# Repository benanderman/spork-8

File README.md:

# Spork-8

This is an 8-bit computer project, inspired by [Ben Eater's 8-bit breadboard computer](https://eater.net/8bit). It's made out of modular PCBs that plug into each other, and contain mostly 74HC-series chips (original 74LS). It runs code from an EEPROM (so it's only programmable from a computer), and has separate memory. It's meant to display what's happening, when running on a 555-timer or manually stepping, but also be capable enough to implement some sort of game, when using an oscillator as a clock.

For details about programming the Spork-8, see [Programming.md](Programming.md).

## Status of project

The project was originally completed in 2021 and mostly worked with 74LS-series chips, but it had some issues (see [RevisionLog](RevisionLog.md)), and used way too much power.

In 2025, it was rebuilt with 74HC-series chips, and several improvements, an emulator, and peripheral boards. It had some issues, but mostly worked well.

In 2026, reliability was improved by adding ground planes to the bus boards and control board, the instruction set was improved, and much more complex programs were made.

## Modules
 * **Control module**: Coordinates everything else. Contains the micro-code EEPROMs, instruction register, micro-instruction counter, power input, reset button, and logic to interface with modules through bus boards.
 * **Bus**: Four of these interface between the control module and up to 16 other modules. These demux three signal lines each for in/out enable signals to the four modules connected to each bus board. One bus board plugs into the top of the control module, and one into the bottom. Two more bus boards plug into the first two. The first in/out signal line selects between the two boards on top / bottom, and the one connected to the control module inverts the signal before passing it onto the other bus board.
 * **Register**: Stores 8 bits, and can connect directly to an adjacent board above or below to expose its value (for use by the ALU and shift / rotate module). Has output headers, to interface with peripherals.
 * **ALU**: Performes calculations on values from register modules above and below it. Can output: add, subtract, bit-wise AND, or the carry-bit and zero-flag for any of those operations. Must be placed in the 1111 position (bottom right of top-most bus board), because the control module is hard-wired to input to the flags register when the read signal to that module position is enabled, which also enables flag output on the ALU.
 * **Clock**: Provides the clock pulse for the computer. Has three modes: manual with button to pulse, 555-timer with potentiometer to adjust timing, or crystal oscillator (2MHz seems to work).
 * **Counter**: Stores and counts 16-bit values. Uses two global signal lines to select which byte to read / write, and whether to enable counting. Used for both the RAM address register and program counter / program memory address register.
 * **RAM**: RAM or EEPROM (they have the same pinout). Used for the program memory EEPROM (not intended to be written to), and the static memory used for storing data. Up to 15-bits of address are taken from an adjacent counter module. Also has a cartridge slot, and switches between it and the EEPROM on the board using the 16th address bit. This allows swapping out programs much easier
 * **Input / Output**: Like a register module, except when outputting to the bus, outputs the value from input headers instead of the registers. The 8-bit value stored in the registers is accessible on output headers as well. The two headers are in parallel, making it sturdy to plug in a peripheral that uses both.
 * **Battery**: Has a battery, charging capability with USB-C, and a switch to output power to the CPU.

## Layout

In general, any of the 16 module slots can input from or output to the bus, so most modules could go in any position. However, some of them have to go in specific slots, because:

1. The 0th slot on the top and bottom aren't usable for in/out selection, because it's ambiguous whether that slot is selected or if no module on that side is selected. The battery and clock go in those slots, since they only output power and a clock signal, and don't use the bus.
1. The 8 "custom" signals (that mean something different for different modules) are split up into 4 for top, 4 for bottom. Those 4 are split into pairs; the top 2 modules on each bus board get one pair, and the bottom two get the second pair. The second pair of signals on the bottom is actually used by the control board.
1. Some modules (RAM / ROM, ALU, and Shift) get inputs from other modules, so their inputs have to be next to them.

**Top left**: The program counter goes in the top to use the first pair of custom signals (for count and byte select), plugging into the program memory below it. Below that is the clock (in the 0th position), and Register C.

**Top right**: The ALU goes one slot down from the top, to use the second pair of custom signals (for add/subtract and bit-wise AND), with register A and B as its operands above and below. Then the shift / rotate module goes at the bottom plugging into register B. These need to be on the right side to avoid the 0th position. The shift module shares custom signals with the ALU, which is okay because only one is used at a time, and the signals don't have an effect if that module isn't outputting.

**Bottom left**: The battery takes the top 0th slot, and then the stack and swap registers, and input / output A module after that. Other than the battery, the positions are arbitrary.

**Bottom right**: The output A register goes at the top and the RAM goes below it. The memory address register goes in the next position to get the first pair of custom signals (for count and byte select), and plugs into the RAM above it. The input / output B module goes at the bottom. The memory address could instead go where output A is, and RAM just needs to be next to it. The other two could go anywhere.

## Peripherals
* **Controller Connector**: Plugs into IO module, and has two RJ12 plugs on it, to connect to parallel-to-serial shift register-based controllers.
* **Screen**: An 10x20 595-shift register-based monochrome display. Plugs into output module (vertically), or IO module (horizontally).
* **Cartridge**: A small board with a surface-mount version of the same 28C256 EEPROM used as in the program memory module. Plugs into the program memory module with the smallest PCIe board edge connector.
* **Programmer**: Arduino-based board used to program and test the CPU in 3 ways:
    1. Separate from the CPU, read / write to EEPROMs (big ones, or cartridges).
    2. Plug into bus boards, to test all the modules plugged in (doesn't work, because the bus is needed to set the signals, but that could cause bus contention).
    3. Replace the program memory and clock, to have a very fast development cycle to write program code (not necessary now that there's an emulator), or to test the CPU.
 
## Layout, signals, and parts list
These images show the layout of the modules in the 16 slots, the functions of each of the signals, and a parts list.

## Design images
### Overall layout

### Mounting board (laser cut acrylic)

### Schematics

### PCB Layouts

### 3D Renderings

## Contributing

### Compiling Assembly Files

Dependency: [customasm](https://hlorenzi.github.io/customasm/)

```
cd Code/emulator
customasm ../programs/snake2p.asm -o ../programs/snake2p.bin -f binary
```

Then pass the .bin files to the emulator.

### Compiling and Running the Emulator

```
cd Code/emulator
zig build
./zig-out/bin/emulator ../programs/snake2p.bin
```

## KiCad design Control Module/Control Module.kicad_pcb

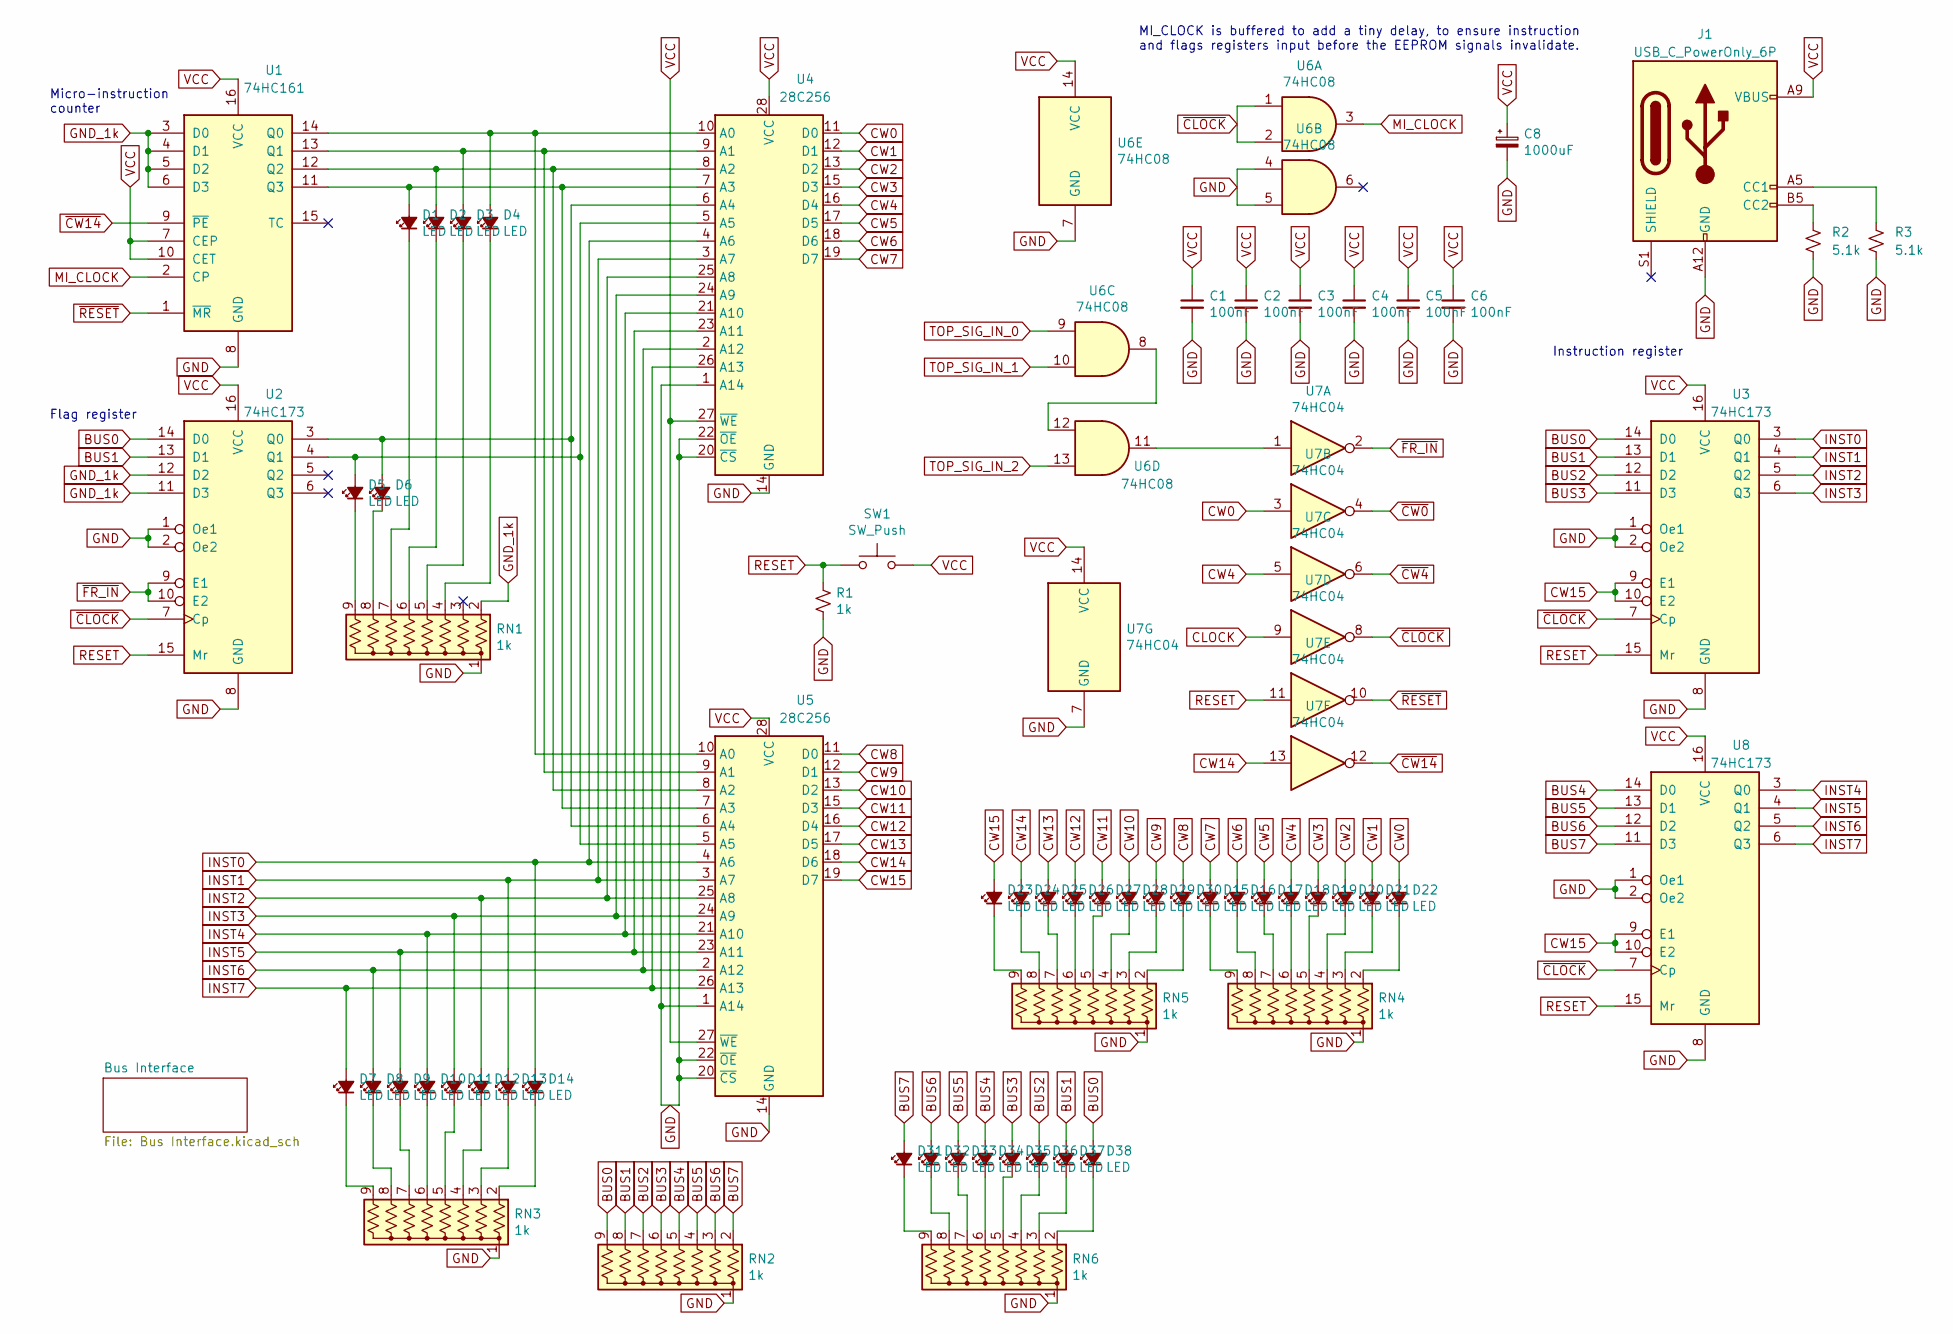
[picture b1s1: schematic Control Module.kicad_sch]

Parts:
C1, C2, C3, C4, C5, C6: 100nF; C_Disc_D4.3mm_W1.9mm_P5.00mm
C8: 1000uF; CP_Radial_D8.0mm_P3.50mm
D1, D2, D3, D4, D5, D6, D7, D8, D9, D10, D11, D12, D13, D14, D15, D16, D17, D18, D19, D20, D21, D22, D23, D24, D25, D26, D27, D28, D29, D30, D31, D32, D33, D34, D35, D36, D37, D38: LED; LED_D3.0mm
J1: USB_C_PowerOnly_6P; USB_C_Receptacle_G-Switch_GT-USB-7010ASV; LCSC C2988369
R1: 1k; R_Axial_DIN0207_L6.3mm_D2.5mm_P7.62mm_Horizontal
R2, R3: 5.1k; R_0603_1608Metric
RN1, RN2, RN3, RN4, RN5, RN6: 1k; R_Array_SIP9
SW1: SW_Push; SW_PUSH_6mm
U1: 74HC161; DIP-16_W7.62mm
U2, U3, U8: 74HC173; DIP-16_W7.62mm
U4, U5: 28C256; DIP-28_W15.24mm_Socket
U6: 74HC08; DIP-14_W7.62mm
U7: 74HC04; DIP-14_W7.62mm

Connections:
BUS0: D38.2 (A), RN2.9 (R8), U2.14 (D0), U3.14 (D0); also elsewhere on the board
BUS1: D37.2 (A), RN2.8 (R7), U2.13 (D1), U3.13 (D1); also elsewhere on the board
BUS2: D36.2 (A), RN2.7 (R6), U3.12 (D2); also elsewhere on the board
BUS3: D35.2 (A), RN2.6 (R5), U3.11 (D3); also elsewhere on the board
BUS4: D34.2 (A), RN2.5 (R4), U8.14 (D0); also elsewhere on the board
BUS5: D33.2 (A), RN2.4 (R3), U8.13 (D1); also elsewhere on the board
BUS6: D32.2 (A), RN2.3 (R2), U8.12 (D2); also elsewhere on the board
BUS7: D31.2 (A), RN2.2 (R1), U8.11 (D3); also elsewhere on the board
CLOCK: U7.9; also elsewhere on the board
CW0: D22.2 (A), U4.11 (D0), U7.3; also elsewhere on the board
CW1: D21.2 (A), U4.12 (D1); also elsewhere on the board
CW2: D20.2 (A), U4.13 (D2); also elsewhere on the board
CW3: D19.2 (A), U4.15 (D3); also elsewhere on the board
CW4: D18.2 (A), U4.16 (D4), U7.5; also elsewhere on the board
CW5: D17.2 (A), U4.17 (D5); also elsewhere on the board
CW6: D16.2 (A), U4.18 (D6); also elsewhere on the board
CW7: D15.2 (A), U4.19 (D7); also elsewhere on the board
CW8: D30.2 (A), U5.11 (D0); also elsewhere on the board
CW9: D29.2 (A), U5.12 (D1); also elsewhere on the board
CW10: D28.2 (A), U5.13 (D2); also elsewhere on the board
CW11: D27.2 (A), U5.15 (D3); also elsewhere on the board
CW12: D26.2 (A), U5.16 (D4); also elsewhere on the board
CW13: D25.2 (A), U5.17 (D5); also elsewhere on the board
CW14: D24.2 (A), U5.18 (D6), U7.13; also elsewhere on the board
CW15: D23.2 (A), U3.9 (E1), U3.10 (E2), U5.19 (D7), U8.9 (E1), U8.10 (E2); also elsewhere on the board
GND: C1.2, C2.2, C3.2, C4.2, C5.2, C6.2, C8.2, J1.A12 (GND), J1.B12 (GND), R1.2, R2.2, R3.2, RN1.1 (common), RN2.1 (common), RN3.1 (common), RN4.1 (common), RN5.1 (common), RN6.1 (common), U1.8 (GND), U2.1 (Oe1), U2.2 (Oe2), U2.8 (GND), U3.1 (Oe1), U3.2 (Oe2), U3.8 (GND), U4.1 (A14), U4.14 (GND), U4.20 (~CS), U4.22 (~OE), U5.1 (A14), U5.14 (GND), U5.20 (~CS), U5.22 (~OE), U6.4, U6.5, U6.7 (GND), U7.7 (GND), U8.1 (Oe1), U8.2 (Oe2), U8.8 (GND); also elsewhere on the board
GND_1k: RN1.2 (R1), U1.3 (D0), U1.4 (D1), U1.5 (D2), U1.6 (D3), U2.11 (D3), U2.12 (D2)
INST0: D14.2 (A), U3.3 (Q0), U4.4 (A6), U5.4 (A6)
INST1: D13.2 (A), U3.4 (Q1), U4.3 (A7), U5.3 (A7)
INST2: D12.2 (A), U3.5 (Q2), U4.25 (A8), U5.25 (A8)
INST3: D11.2 (A), U3.6 (Q3), U4.24 (A9), U5.24 (A9)
INST4: D10.2 (A), U4.21 (A10), U5.21 (A10), U8.3 (Q0)
INST5: D9.2 (A), U4.23 (A11), U5.23 (A11), U8.4 (Q1)
INST6: D8.2 (A), U4.2 (A12), U5.2 (A12), U8.5 (Q2)
INST7: D7.2 (A), U4.26 (A13), U5.26 (A13), U8.6 (Q3)
MI_CLOCK: U1.2 (CP), U6.3
unnamed: D1.2 (A), U1.11 (Q3), U4.7 (A3), U5.7 (A3)
unnamed: D1.1 (K), RN1.7 (R6)
unnamed: D2.2 (A), U1.12 (Q2), U4.8 (A2), U5.8 (A2)
unnamed: D2.1 (K), RN1.6 (R5)
unnamed: D3.2 (A), U1.13 (Q1), U4.9 (A1), U5.9 (A1)
unnamed: D3.1 (K), RN1.5 (R4)
unnamed: D4.2 (A), U1.14 (Q0), U4.10 (A0), U5.10 (A0)
unnamed: D4.1 (K), RN1.4 (R3)
unnamed: D5.2 (A), U2.4 (Q1), U4.5 (A5), U5.5 (A5)
unnamed: D5.1 (K), RN1.9 (R8)
unnamed: D6.2 (A), U2.3 (Q0), U4.6 (A4), U5.6 (A4)
unnamed: D6.1 (K), RN1.8 (R7)
unnamed: D7.1 (K), RN3.9 (R8)
unnamed: D8.1 (K), RN3.8 (R7)
unnamed: D9.1 (K), RN3.7 (R6)
unnamed: D10.1 (K), RN3.6 (R5)
unnamed: D11.1 (K), RN3.5 (R4)
unnamed: D12.1 (K), RN3.4 (R3)
unnamed: D13.1 (K), RN3.3 (R2)
unnamed: D14.1 (K), RN3.2 (R1)
unnamed: D15.1 (K), RN4.9 (R8)
unnamed: D16.1 (K), RN4.8 (R7)
unnamed: D17.1 (K), RN4.7 (R6)
unnamed: D18.1 (K), RN4.6 (R5)
unnamed: D19.1 (K), RN4.5 (R4)
unnamed: D20.1 (K), RN4.4 (R3)
unnamed: D21.1 (K), RN4.3 (R2)
unnamed: D22.1 (K), RN4.2 (R1)
unnamed: D23.1 (K), RN5.9 (R8)
unnamed: D24.1 (K), RN5.8 (R7)
unnamed: D25.1 (K), RN5.7 (R6)
unnamed: D26.1 (K), RN5.6 (R5)
unnamed: D27.1 (K), RN5.5 (R4)
unnamed: D28.1 (K), RN5.4 (R3)
unnamed: D29.1 (K), RN5.3 (R2)
unnamed: D30.1 (K), RN5.2 (R1)
unnamed: D31.1 (K), RN6.9 (R8)
unnamed: D32.1 (K), RN6.8 (R7)
unnamed: D33.1 (K), RN6.7 (R6)
unnamed: D34.1 (K), RN6.6 (R5)
unnamed: D35.1 (K), RN6.5 (R4)
unnamed: D36.1 (K), RN6.4 (R3)
unnamed: D37.1 (K), RN6.3 (R2)
unnamed: D38.1 (K), RN6.2 (R1)
unnamed: J1.A5 (CC1), R3.1
unnamed: J1.B5 (CC2), R2.1
unnamed: U6.11, U7.1
unnamed: U6.8, U6.12
RESET: R1.1, SW1.1, U2.15 (Mr), U3.15 (Mr), U7.11, U8.15 (Mr); also elsewhere on the board
TOP_SIG_IN_0: U6.9; also elsewhere on the board
TOP_SIG_IN_1: U6.10; also elsewhere on the board
TOP_SIG_IN_2: U6.13; also elsewhere on the board
VCC: C1.1, C2.1, C3.1, C4.1, C5.1, C6.1, C8.1, J1.A9 (VBUS), J1.B9 (VBUS), SW1.2, U1.7 (CEP), U1.10 (CET), U1.16 (VCC), U2.16 (VCC), U3.16 (VCC), U4.27 (~WE), U4.28 (VCC), U5.27 (~WE), U5.28 (VCC), U6.14 (VCC), U7.14 (VCC), U8.16 (VCC); also elsewhere on the board
~CLOCK: U2.7 (Cp), U3.7 (Cp), U6.1, U6.2, U7.8, U8.7 (Cp)
~CW0: U7.4; also elsewhere on the board
~CW4: U7.6; also elsewhere on the board
~CW14: U1.9 (~PE), U7.12
~FR_IN: U2.9 (E1), U2.10 (E2), U7.2
~RESET: U1.1 (~MR), U7.10

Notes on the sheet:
Micro-instruction counter
MI_CLOCK is buffered to add a tiny delay, to ensure instruction and flags registers input before the EEPROM signals invalidate.
Flag register
Instruction register

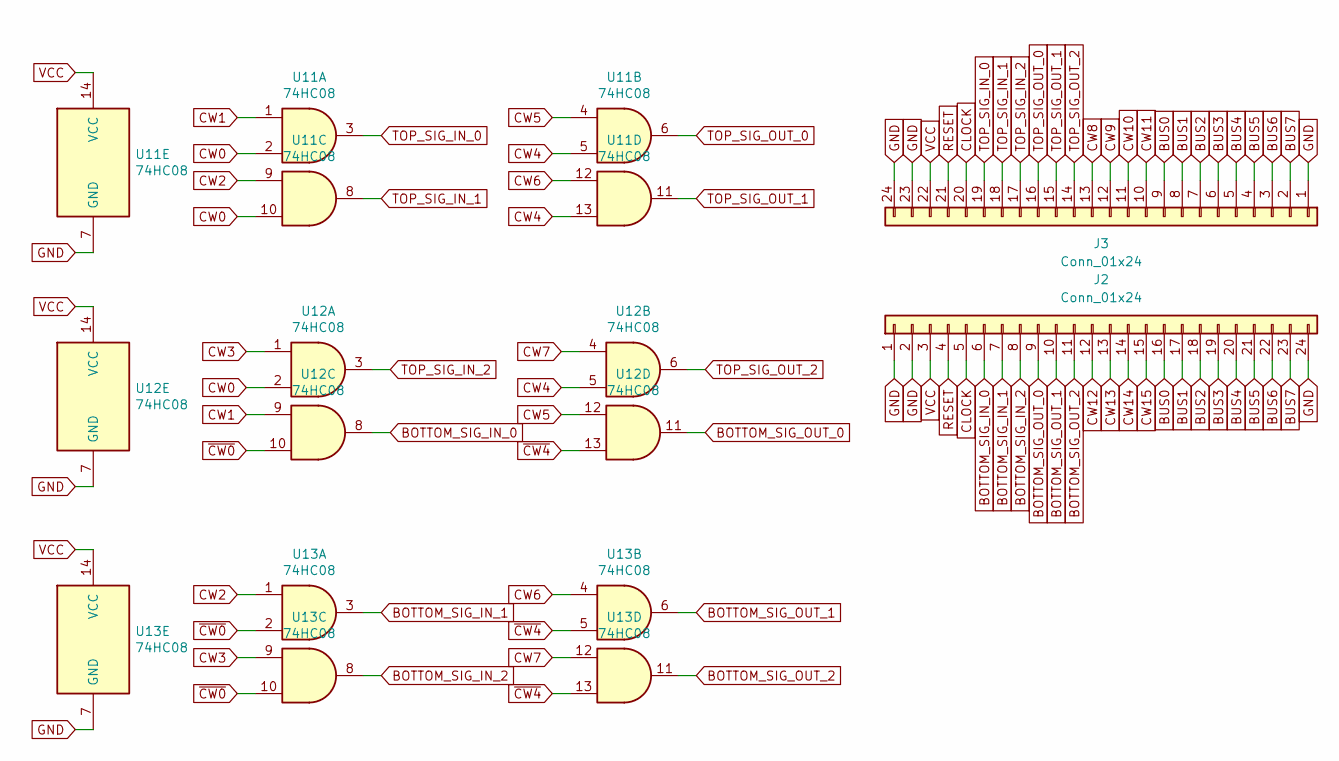
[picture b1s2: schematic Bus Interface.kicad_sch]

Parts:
J2, J3: Conn_01x24; PinSocket_1x24_P2.54mm_Horizontal
U11, U12, U13: 74HC08; DIP-14_W7.62mm

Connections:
BOTTOM_SIG_IN_0: J2.6, U12.8
BOTTOM_SIG_IN_1: J2.7, U13.3
BOTTOM_SIG_IN_2: J2.8, U13.8
BOTTOM_SIG_OUT_0: J2.9, U12.11
BOTTOM_SIG_OUT_1: J2.10, U13.6
BOTTOM_SIG_OUT_2: J2.11, U13.11
BUS0: J2.16, J3.9; also elsewhere on the board
BUS1: J2.17, J3.8; also elsewhere on the board
BUS2: J2.18, J3.7; also elsewhere on the board
BUS3: J2.19, J3.6; also elsewhere on the board
BUS4: J2.20, J3.5; also elsewhere on the board
BUS5: J2.21, J3.4; also elsewhere on the board
BUS6: J2.22, J3.3; also elsewhere on the board
BUS7: J2.23, J3.2; also elsewhere on the board
CLOCK: J2.5, J3.20; also elsewhere on the board
CW0: U11.2, U11.10, U12.2; also elsewhere on the board
CW1: U11.1, U12.9; also elsewhere on the board
CW2: U11.9, U13.1; also elsewhere on the board
CW3: U12.1, U13.9; also elsewhere on the board
CW4: U11.5, U11.13, U12.5; also elsewhere on the board
CW5: U11.4, U12.12; also elsewhere on the board
CW6: U11.12, U13.4; also elsewhere on the board
CW7: U12.4, U13.12; also elsewhere on the board
CW8: J3.13; also elsewhere on the board
CW9: J3.12; also elsewhere on the board
CW10: J3.11; also elsewhere on the board
CW11: J3.10; also elsewhere on the board
CW12: J2.12; also elsewhere on the board
CW13: J2.13; also elsewhere on the board
CW14: J2.14; also elsewhere on the board
CW15: J2.15; also elsewhere on the board
GND: J2.1, J2.2, J2.24, J3.1, J3.23, J3.24, U11.7 (GND), U12.7 (GND), U13.7 (GND); also elsewhere on the board
RESET: J2.4, J3.21; also elsewhere on the board
TOP_SIG_IN_0: J3.19, U11.3; also elsewhere on the board
TOP_SIG_IN_1: J3.18, U11.8; also elsewhere on the board
TOP_SIG_IN_2: J3.17, U12.3; also elsewhere on the board
TOP_SIG_OUT_0: J3.16, U11.6
TOP_SIG_OUT_1: J3.15, U11.11
TOP_SIG_OUT_2: J3.14, U12.6
VCC: J2.3, J3.22, U11.14 (VCC), U12.14 (VCC), U13.14 (VCC); also elsewhere on the board
~CW0: U12.10, U13.2, U13.10; also elsewhere on the board
~CW4: U12.13, U13.5, U13.13; also elsewhere on the board

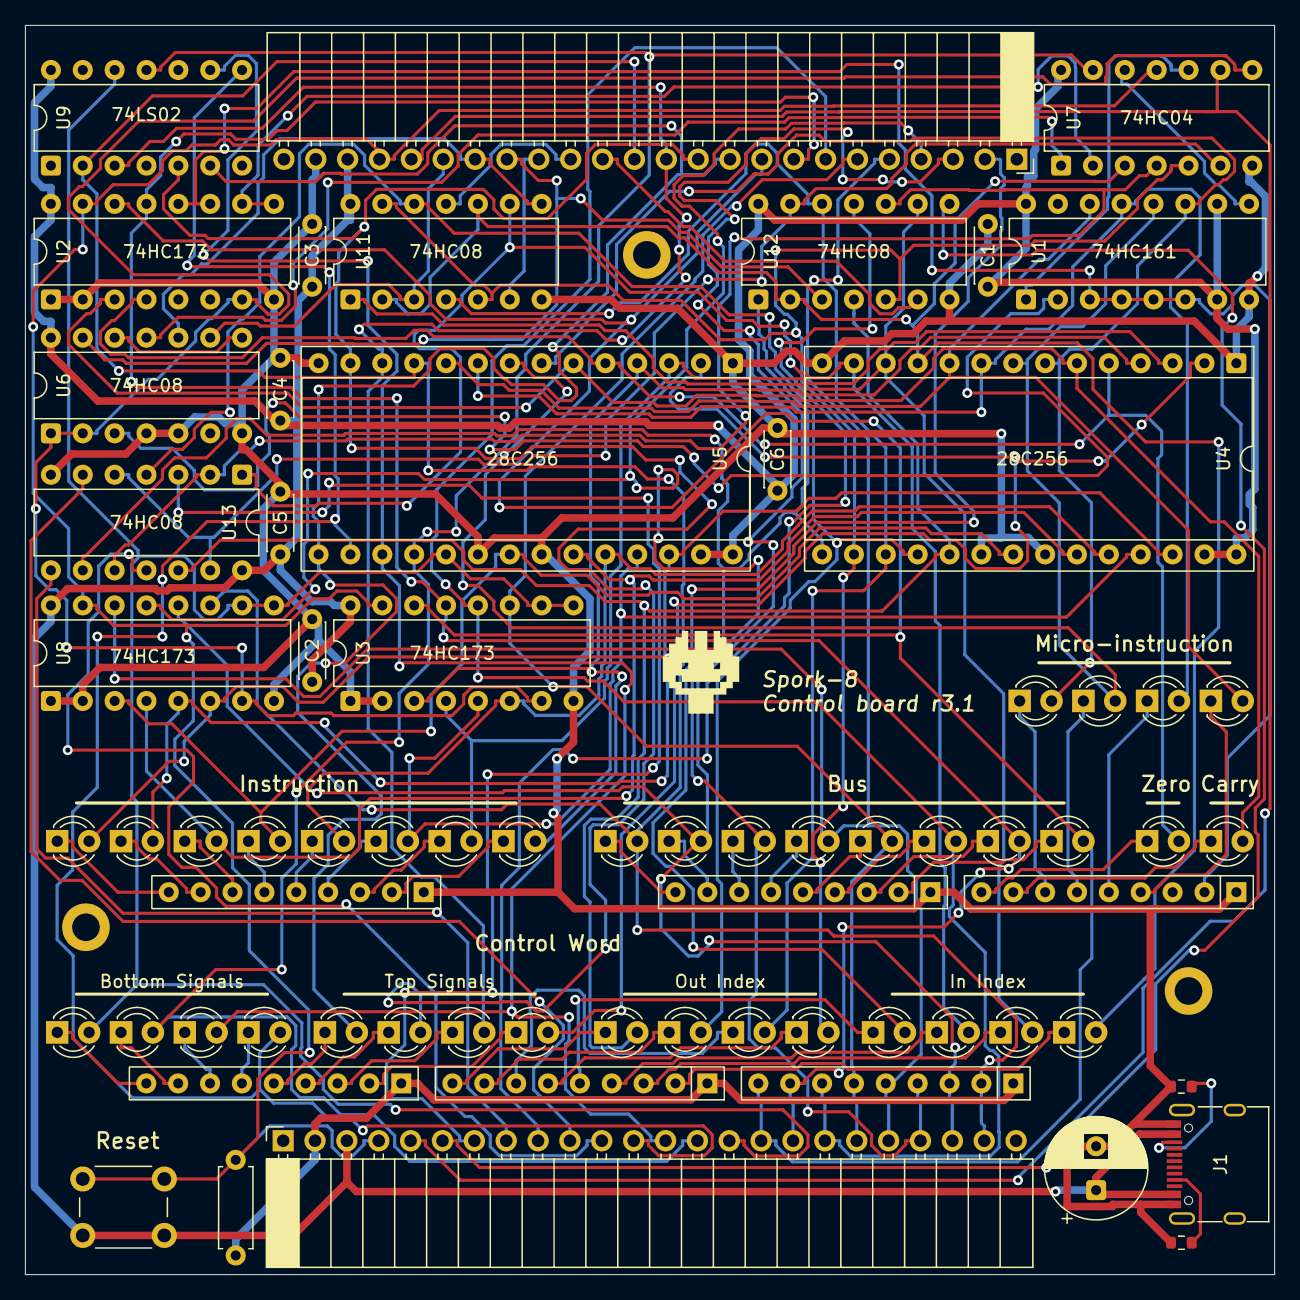
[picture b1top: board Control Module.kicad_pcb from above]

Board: 4 copper layers, 99.6 x 99.6 mm, 73 parts (0 on the bottom side), 104 nets.

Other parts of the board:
HOLE1, HOLE2, HOLE3: MountingHole_2.2mm_M2_DIN965_Pad
U9: 74LS02; DIP-14_W7.62mm

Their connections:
CW8: U9.2; also elsewhere on the board
CW9: U9.3; also elsewhere on the board
CW10: U9.5; also elsewhere on the board
CW11: U9.6; also elsewhere on the board
CW12: U9.8; also elsewhere on the board
CW13: U9.9; also elsewhere on the board
CW14: U9.11; also elsewhere on the board
CW15: U9.12; also elsewhere on the board
GND: U9.7; also elsewhere on the board
VCC: U9.14; also elsewhere on the board

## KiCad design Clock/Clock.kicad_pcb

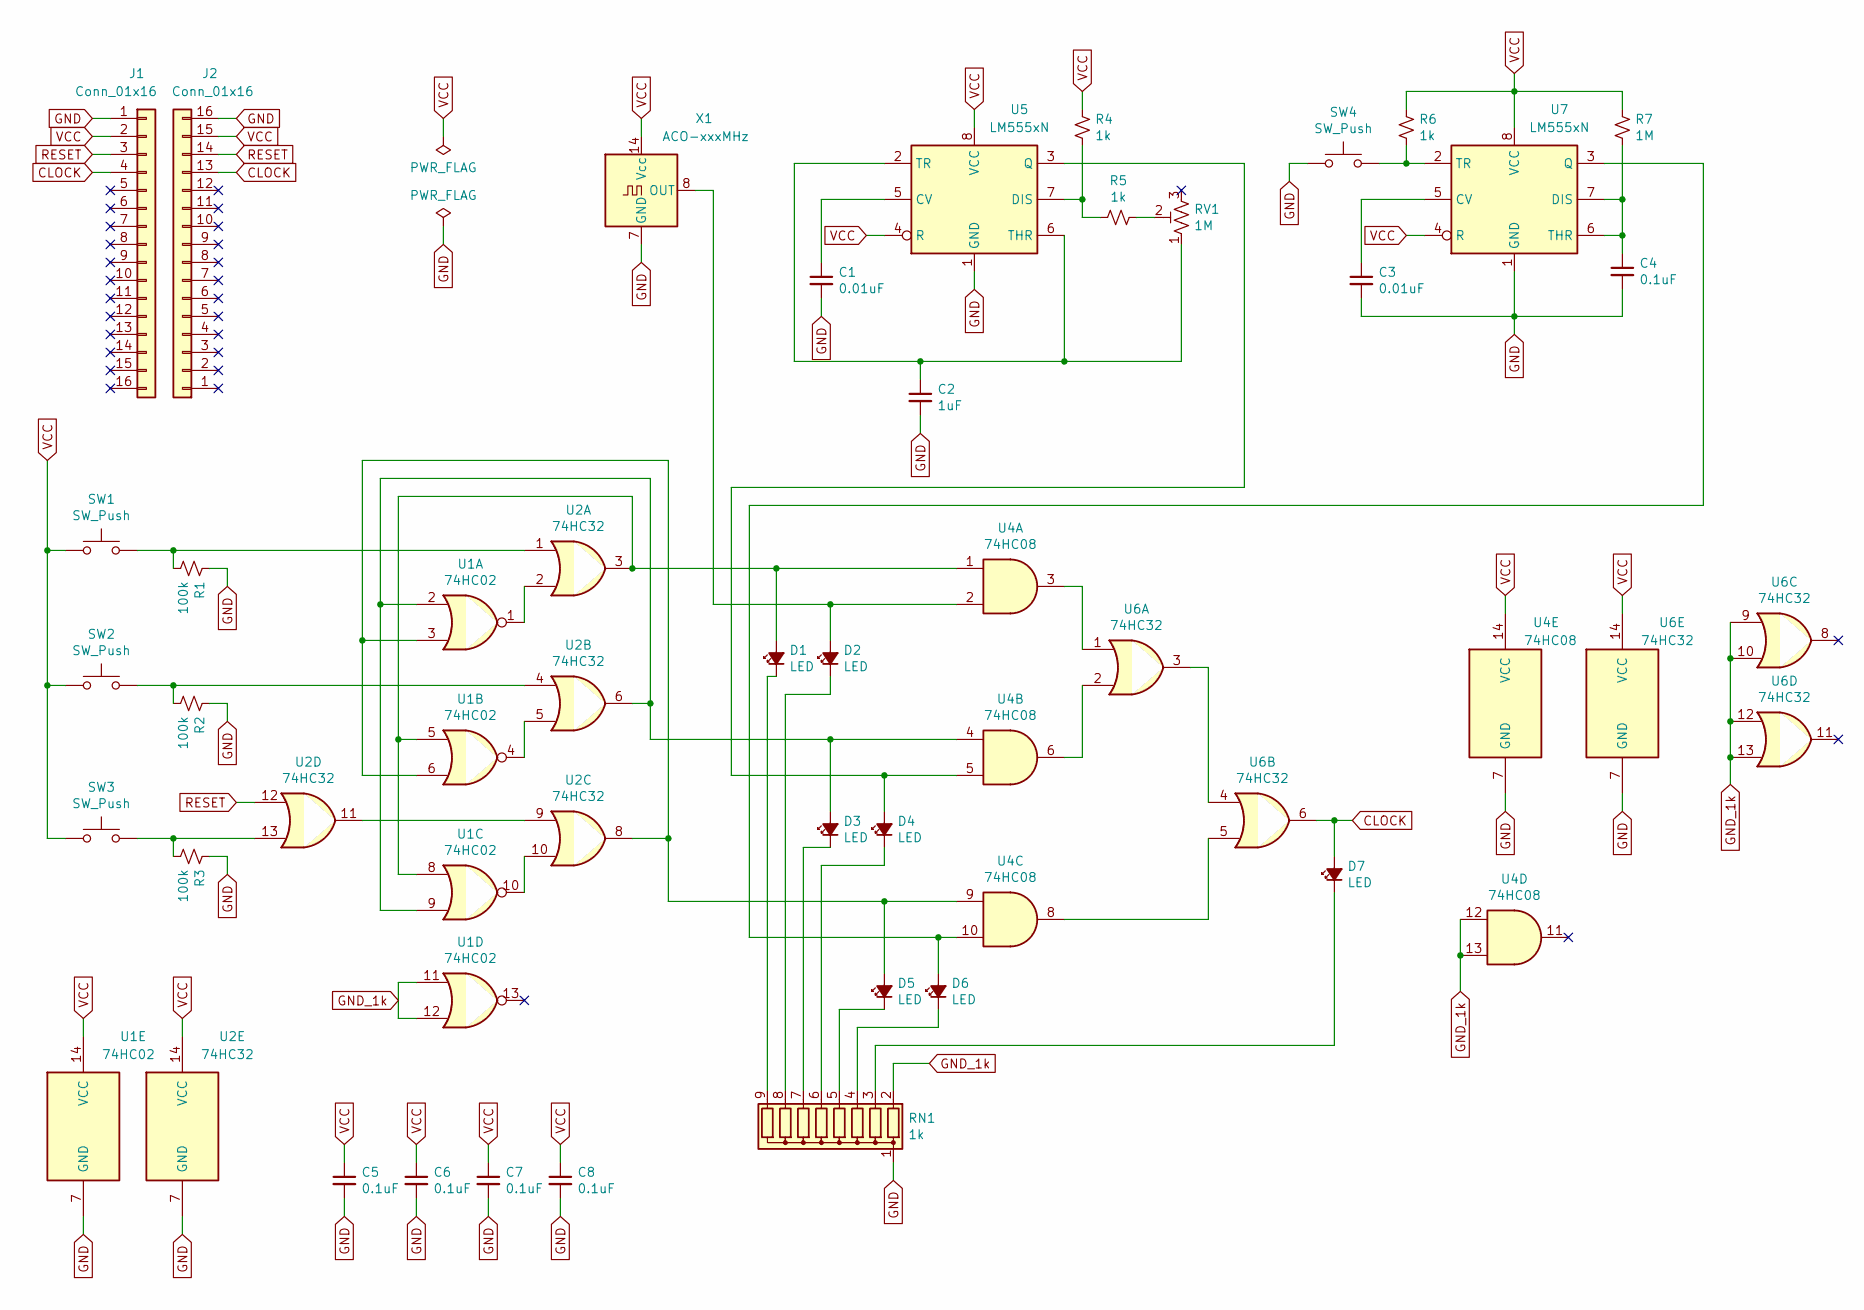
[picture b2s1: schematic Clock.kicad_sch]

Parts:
C1, C3: 0.01uF; C_Disc_D4.3mm_W1.9mm_P5.00mm
C2: 1uF; C_Disc_D4.3mm_W1.9mm_P5.00mm
C4, C5, C6, C7, C8: 0.1uF; C_Disc_D4.3mm_W1.9mm_P5.00mm
D1, D2, D3, D4, D5, D6, D7: LED; LED_D3.0mm_Clear
J1, J2: Conn_01x16; PinHeader_1x16_P2.54mm_Horizontal
R1, R2, R3: 100k; R_Axial_DIN0207_L6.3mm_D2.5mm_P7.62mm_Horizontal
R4, R5, R6: 1k; R_Axial_DIN0207_L6.3mm_D2.5mm_P7.62mm_Horizontal
R7: 1M; R_Axial_DIN0207_L6.3mm_D2.5mm_P7.62mm_Horizontal
RN1: 1k; R_Array_SIP9
RV1: 1M; Potentiometer_Bourns_PTV09A-1_Single_Vertical
SW1, SW2, SW3, SW4: SW_Push; SW_PUSH_6mm
U1: 74HC02; DIP-14_W7.62mm
U2, U6: 74HC32; DIP-14_W7.62mm
U4: 74HC08; DIP-14_W7.62mm
U5, U7: LM555xN; DIP-8_W7.62mm
X1: ACO-xxxMHz; Oscillator_DIP-14

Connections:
CLOCK: D7.2 (A), J1.4, J2.13, U6.6
GND: C1.2, C2.2, C3.2, C4.2, C5.2, C6.2, C7.2, C8.2, J1.1, J2.16, R1.1, R2.1, R3.1, RN1.1 (common), SW4.1, U1.7 (GND), U2.7 (GND), U4.7 (GND), U5.1 (GND), U6.7 (GND), U7.1 (GND), X1.7 (GND)
GND_1k: RN1.2 (R1), U1.11, U1.12, U4.12, U4.13, U6.9, U6.10, U6.12, U6.13
unnamed: D1.2 (A), U1.5, U1.8, U2.3, U4.1
unnamed: D1.1 (K), RN1.9 (R8)
unnamed: D2.2 (A), U4.2, X1.8 (OUT)
unnamed: D2.1 (K), RN1.8 (R7)
unnamed: D3.2 (A), U1.2, U1.9, U2.6, U4.4
unnamed: D3.1 (K), RN1.7 (R6)
unnamed: D4.2 (A), U4.5, U5.3 (Q)
unnamed: D4.1 (K), RN1.6 (R5)
unnamed: D5.2 (A), U1.3, U1.6, U2.8, U4.9
unnamed: D5.1 (K), RN1.5 (R4)
unnamed: D6.2 (A), U4.10, U7.3 (Q)
unnamed: D6.1 (K), RN1.4 (R3)
unnamed: D7.1 (K), RN1.3 (R2)
unnamed: R1.2, SW1.2, U2.1
unnamed: R2.2, SW2.2, U2.4
unnamed: R3.2, SW3.2, U2.13
unnamed: R5.1, RV1.2
unnamed: U1.1, U2.2
unnamed: U1.4, U2.5
unnamed: U1.10, U2.10
unnamed: U2.9, U2.11
unnamed: U4.3, U6.1
unnamed: U4.6, U6.2
unnamed: U4.8, U6.5
unnamed: C1.1, U5.5 (CV)
unnamed: R4.1, R5.2, U5.7 (DIS)
unnamed: C2.1, RV1.1, U5.2 (TR), U5.6 (THR)
unnamed: U6.3, U6.4
unnamed: C3.1, U7.5 (CV)
unnamed: C4.1, R7.1, U7.6 (THR), U7.7 (DIS)
unnamed: R6.1, SW4.2, U7.2 (TR)
RESET: J1.3, J2.14, U2.12
VCC: C5.1, C6.1, C7.1, C8.1, J1.2, J2.15, R4.2, R6.2, R7.2, SW1.1, SW2.1, SW3.1, U1.14 (VCC), U2.14 (VCC), U4.14 (VCC), U5.4 (R), U5.8 (VCC), U6.14 (VCC), U7.4 (R), U7.8 (VCC), X1.14 (Vcc)

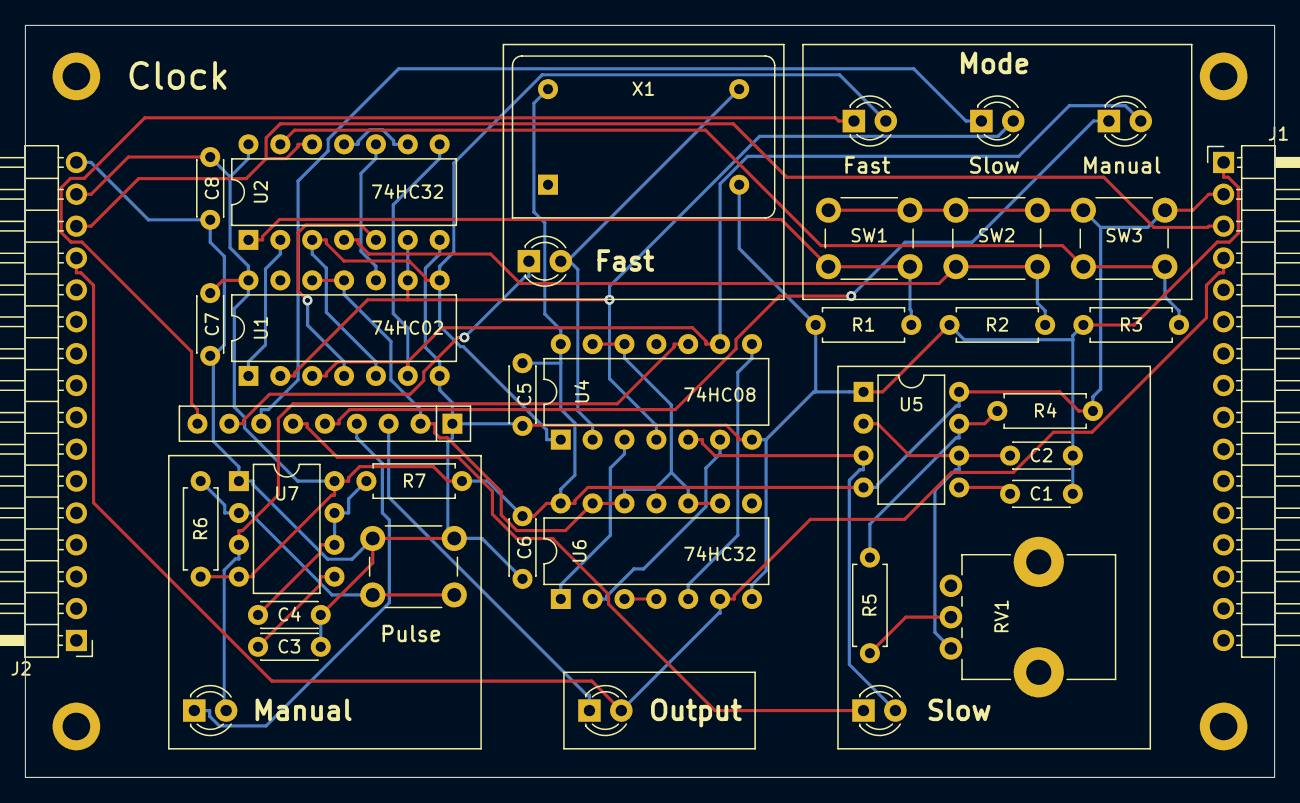
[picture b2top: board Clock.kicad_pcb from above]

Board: 2 copper layers, 99.6 x 59.9 mm, 41 parts (0 on the bottom side), 36 nets.

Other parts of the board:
HOLE1, HOLE2, HOLE3, HOLE4: MountingHole_2.2mm_M2_DIN965_Pad

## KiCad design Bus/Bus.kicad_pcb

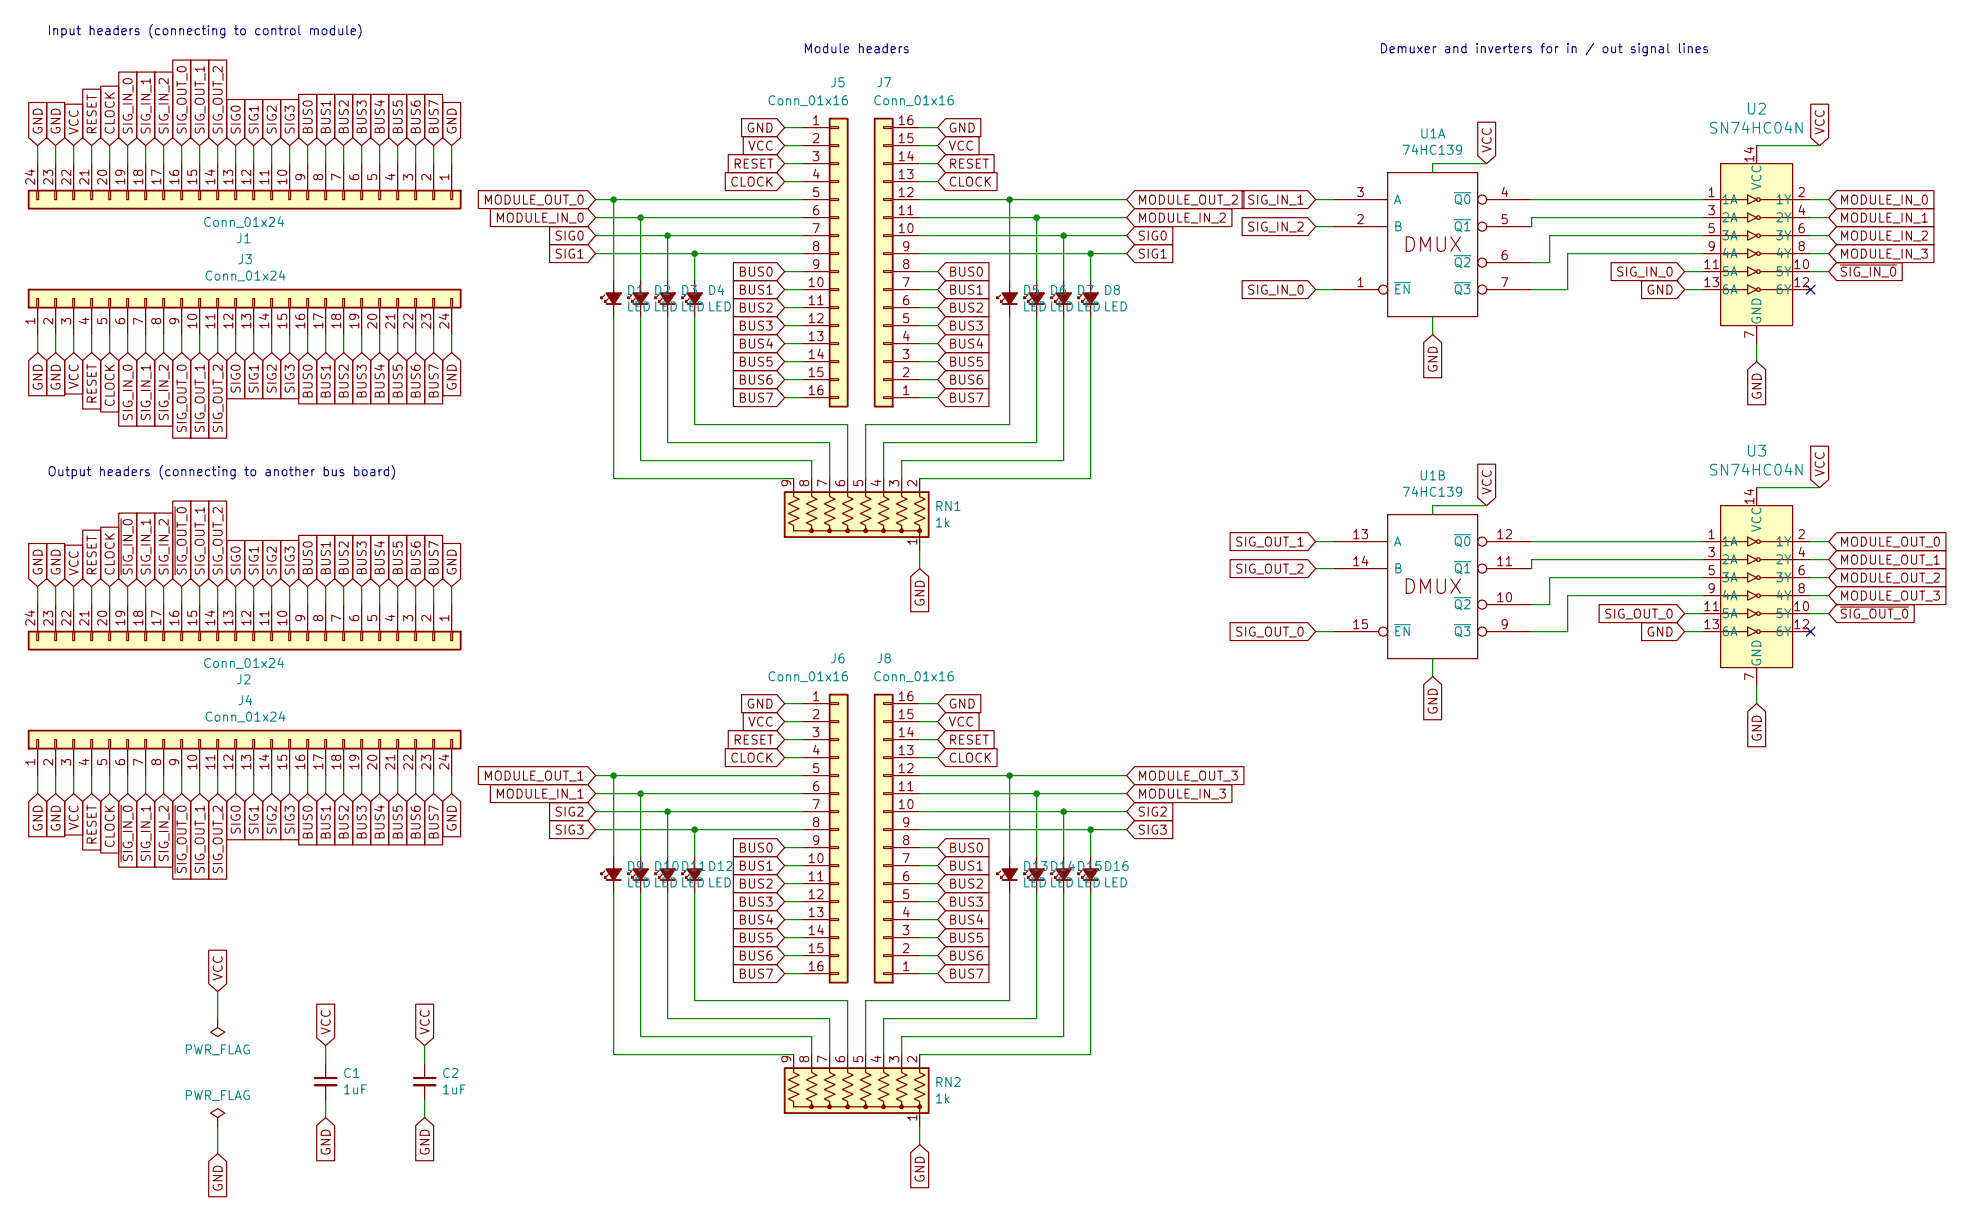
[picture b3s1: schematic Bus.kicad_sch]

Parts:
C1, C2: 1uF; C_Disc_D3.4mm_W2.1mm_P2.50mm
D1, D2, D3, D4, D5, D6, D7, D8, D9, D10, D11, D12, D13, D14, D15, D16: LED; LED_D3.0mm_Clear
J1, J3: Conn_01x24; PinHeader_1x24_P2.54mm_Horizontal
J2, J4: Conn_01x24; PinSocket_1x24_P2.54mm_Horizontal
J5, J6, J7, J8: Conn_01x16; PinSocket_1x16_P2.54mm_Horizontal
RN1, RN2: 1k; R_Array_SIP9
U1: 74HC139; DIP-16_W7.62mm
U2, U3: SN74HC04N; DIP-14_W7.62mm; MPN SN74LS04N; Digi-Key_PN 296-1629-5-ND

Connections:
BUS0: J1.9, J2.9, J3.16, J4.16, J5.9, J6.9, J7.8, J8.8
BUS1: J1.8, J2.8, J3.17, J4.17, J5.10, J6.10, J7.7, J8.7
BUS2: J1.7, J2.7, J3.18, J4.18, J5.11, J6.11, J7.6, J8.6
BUS3: J1.6, J2.6, J3.19, J4.19, J5.12, J6.12, J7.5, J8.5
BUS4: J1.5, J2.5, J3.20, J4.20, J5.13, J6.13, J7.4, J8.4
BUS5: J1.4, J2.4, J3.21, J4.21, J5.14, J6.14, J7.3, J8.3
BUS6: J1.3, J2.3, J3.22, J4.22, J5.15, J6.15, J7.2, J8.2
BUS7: J1.2, J2.2, J3.23, J4.23, J5.16, J6.16, J7.1, J8.1
CLOCK: J1.20, J2.20, J3.5, J4.5, J5.4, J6.4, J7.13, J8.13
GND: C1.2, C2.2, J1.1, J1.23, J1.24, J2.1, J2.23, J2.24, J3.1, J3.2, J3.24, J4.1, J4.2, J4.24, J5.1, J6.1, J7.16, J8.16, RN1.1 (common), RN2.1 (common), U1.8 (GND), U2.7 (GND), U2.13 (6A), U3.7 (GND), U3.13 (6A)
MODULE_IN_0: D2.2 (A), J5.6, U2.2 (1Y)
MODULE_IN_1: D10.2 (A), J6.6, U2.4 (2Y)
MODULE_IN_2: D6.2 (A), J7.11, U2.6 (3Y)
MODULE_IN_3: D14.2 (A), J8.11, U2.8 (4Y)
MODULE_OUT_0: D1.2 (A), J5.5, U3.2 (1Y)
MODULE_OUT_1: D9.2 (A), J6.5, U3.4 (2Y)
MODULE_OUT_2: D5.2 (A), J7.12, U3.6 (3Y)
MODULE_OUT_3: D13.2 (A), J8.12, U3.8 (4Y)
unnamed: D1.1 (K), RN1.9 (R8)
unnamed: D2.1 (K), RN1.8 (R7)
unnamed: D3.1 (K), RN1.7 (R6)
unnamed: D4.1 (K), RN1.6 (R5)
unnamed: D5.1 (K), RN1.5 (R4)
unnamed: D6.1 (K), RN1.4 (R3)
unnamed: D7.1 (K), RN1.3 (R2)
unnamed: D8.1 (K), RN1.2 (R1)
unnamed: D9.1 (K), RN2.9 (R8)
unnamed: D10.1 (K), RN2.8 (R7)
unnamed: D11.1 (K), RN2.7 (R6)
unnamed: D12.1 (K), RN2.6 (R5)
unnamed: D13.1 (K), RN2.5 (R4)
unnamed: D14.1 (K), RN2.4 (R3)
unnamed: D15.1 (K), RN2.3 (R2)
unnamed: D16.1 (K), RN2.2 (R1)
unnamed: U1.4 (~Q0), U2.1 (1A)
unnamed: U1.5 (~Q1), U2.3 (2A)
unnamed: U1.6 (~Q2), U2.5 (3A)
unnamed: U1.7 (~Q3), U2.9 (4A)
unnamed: U1.12 (~Q0), U3.1 (1A)
unnamed: U1.11 (~Q1), U3.3 (2A)
unnamed: U1.10 (~Q2), U3.5 (3A)
unnamed: U1.9 (~Q3), U3.9 (4A)
RESET: J1.21, J2.21, J3.4, J4.4, J5.3, J6.3, J7.14, J8.14
SIG0: D3.2 (A), D7.2 (A), J1.13, J2.13, J3.12, J4.12, J5.7, J7.10
SIG1: D4.2 (A), D8.2 (A), J1.12, J2.12, J3.13, J4.13, J5.8, J7.9
SIG2: D11.2 (A), D15.2 (A), J1.11, J2.11, J3.14, J4.14, J6.7, J8.10
SIG3: D12.2 (A), D16.2 (A), J1.10, J2.10, J3.15, J4.15, J6.8, J8.9
SIG_IN_0: J1.19, J3.6, U1.1 (~EN), U2.11 (5A)
SIG_IN_1: J1.18, J2.18, J3.7, J4.7, U1.3 (A)
SIG_IN_2: J1.17, J2.17, J3.8, J4.8, U1.2 (B)
SIG_OUT_0: J1.16, J3.9, U1.15 (~EN), U3.11 (5A)
SIG_OUT_1: J1.15, J2.15, J3.10, J4.10, U1.13 (A)
SIG_OUT_2: J1.14, J2.14, J3.11, J4.11, U1.14 (B)
VCC: C1.1, C2.1, J1.22, J2.22, J3.3, J4.3, J5.2, J6.2, J7.15, J8.15, U1.16 (VCC), U2.14 (VCC), U3.14 (VCC)
~SIG_IN_0: J2.19, J4.6, U2.10 (5Y)
~SIG_OUT_0: J2.16, J4.9, U3.10 (5Y)

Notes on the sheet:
Module headers
Output headers (connecting to another bus board)
Input headers (connecting to control module)
Demuxer and inverters for in / out signal lines
